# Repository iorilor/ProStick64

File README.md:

# ProStick64

This repository contains everything about the ProStick64 stick replacement module and more!
This is what you can find inside the various folders:
* datasheets:     datasheets of the various electronic components used on the board
* documentation:  useful documents and application notes regarding the STM32G0 MCU
* media:          Images and other media related to ProStick64
* PCB:            PCB gerber files, KICAD project and libraries
* render:         STL files of the enclosure and thumbstick
* source:         Source code of the software

Note: if you want to edit the source code I suggest you to import the source folders inside STM32CubeIDE software.
For any additional info contact me at info@prostick64.com

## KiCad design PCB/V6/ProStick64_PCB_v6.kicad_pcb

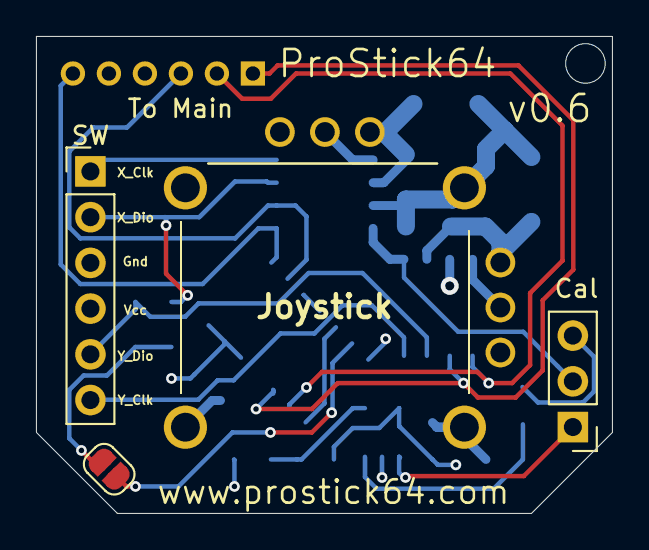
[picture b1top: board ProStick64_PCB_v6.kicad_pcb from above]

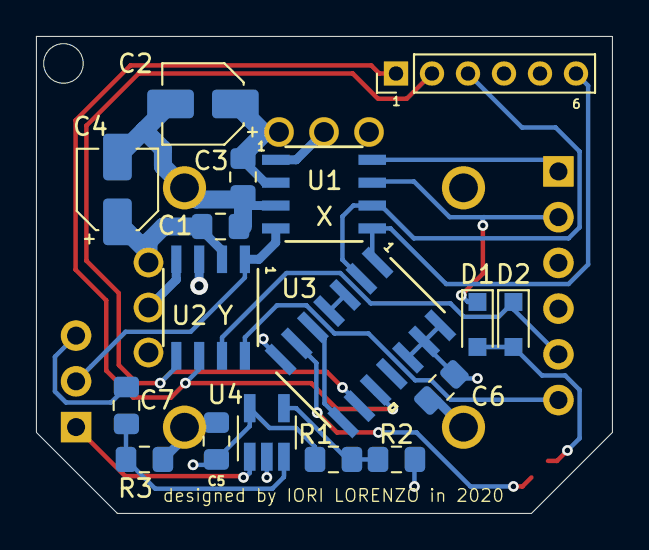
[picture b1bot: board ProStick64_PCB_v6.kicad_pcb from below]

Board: 4 copper layers, 32.0 x 26.5 mm, 21 parts (17 on the bottom side), 20 nets.

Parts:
C1, C3, C5, C6, C7: 0.1uF; C_0805_2012Metric_Pad1.15x1.40mm_HandSolder
C2, C4: 4.7uF; CP_Elec_4x5.3
Cal: CAL_SW; PinHeader_1x03_P2.54mm_Vertical
D1, D2: BAS316; D_SOD-323_HandSoldering
JP1: SolderJumper_2_Open; SolderJumper-2_P1.3mm_Open_RoundedPad1.0x1.5mm
Joystick: RKJXK122000D
R1: 4.75k; R_0805_2012Metric_Pad1.15x1.40mm_HandSolder
R2, R3: 30k; R_0805_2012Metric_Pad1.15x1.40mm_HandSolder
SW: Serial Wire; PinHeader_1x06_P2.54mm_Vertical
To Main: TO MAIN BOARD; PinHeader_1x06_P2.00mm_Vertical
U1: X; STM32G0_SO8_T2
U2: Y; STM32G0_SO8_T2
U3: CD74HC08M
U4: TS861AIL; SOT-23-5_HandSoldering

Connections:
/Vcc: C1.1, C2.1, C3.1, C4.1, C5.1, C6.1, C7.1, Cal.3, Joystick.3, Joystick.6, R1.2, SW.4, To Main.5, U1.2, U2.2, U3.12, U3.13, U3.14, U4.5
/X0: To Main.6, U1.5, U3.1
/X1: To Main.3, U1.6, U3.2
/Y0: To Main.2, U2.5, U3.9
/Y1: To Main.1, U2.6, U3.10
/cal: Cal.2, U1.4, U2.1
/x_dio: D1.1, SW.2, U1.7
/y_dio: D2.1, SW.5, U2.7
GND: C1.2, C2.2, C3.2, C4.2, C5.2, C6.2, Joystick.1, Joystick.4, Joystick.GND, R2.1, R3.2, SW.3, To Main.4, U1.3, U2.3, U3.7, U4.2
unnamed: C7.2, R3.1, U4.3
unnamed: D1.2, D2.2, JP1.1
unnamed: SW.1, U1.8
unnamed: SW.6, U2.8
unnamed: Cal.1, U4.1
unnamed: JP1.2, U3.6
unnamed: R1.1, R2.2, U4.4
unnamed: Joystick.2, U1.1
unnamed: Joystick.5, U2.4
unnamed: U3.3, U3.4
unnamed: U3.5, U3.8

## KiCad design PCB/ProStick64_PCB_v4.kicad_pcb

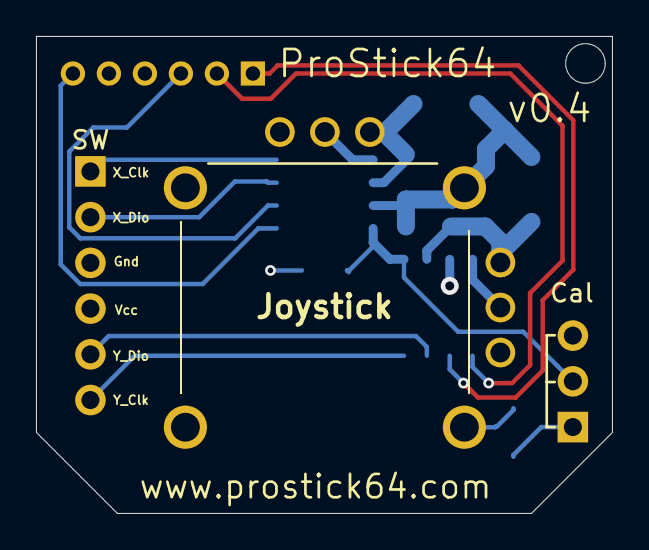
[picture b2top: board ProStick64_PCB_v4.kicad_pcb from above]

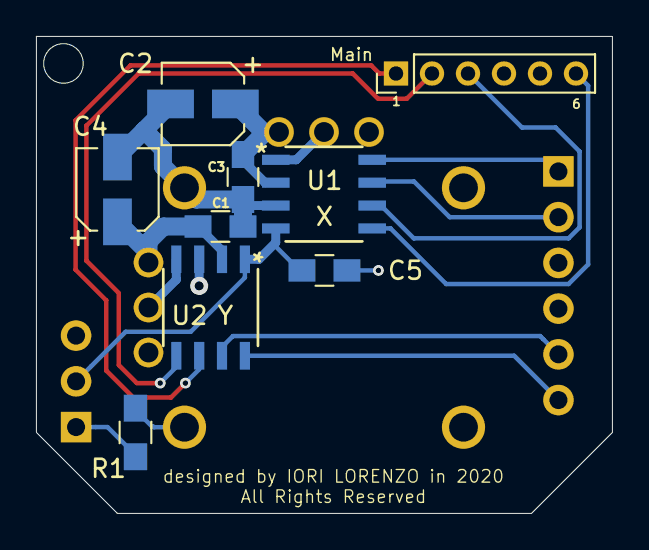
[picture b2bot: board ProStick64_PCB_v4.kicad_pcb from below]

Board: 4 copper layers, 32.0 x 26.5 mm, 12 parts (9 on the bottom side), 14 nets.

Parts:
C1, C3, C5: 0.1uF; C_0805_HandSoldering
C2, C4: 4.7uF; CP_Elec_4x5.3
Cal: CAL_SW; Pin_Header_Straight_1x03_Pitch2.54mm
Joystick: RKJXK122000D
Main: TO MAIN BOARD; Pin_Header_Straight_1x06_Pitch2.00mm
R1: 30k; R_0805_HandSoldering
SW: Serial Wire; Pin_Header_Straight_1x06_Pitch2.54mm
U1: X; STM32G0_SO8_T2
U2: Y; STM32G0_SO8_T2

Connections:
GND: C1.2, C2.2, C3.2, C4.2, Joystick.1, Joystick.4, Main.4, R1.1, SW.3, U1.3, U2.3
unnamed: C1.1, C2.1, C3.1, C4.1, C5.2, Cal.3, Joystick.3, Joystick.6, Main.5, SW.4, U1.2, U2.2
unnamed: C5.1, Cal.2, U1.4, U2.1
unnamed: SW.1, U1.8
unnamed: SW.2, U1.7
unnamed: SW.5, U2.7
unnamed: SW.6, U2.8
unnamed: Cal.1, R1.2
unnamed: Main.1, U2.6
unnamed: Main.2, U2.5
unnamed: Main.3, U1.6
unnamed: Main.6, U1.5
unnamed: Joystick.2, U1.1
unnamed: Joystick.5, U2.4

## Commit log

2020-07-22 Applied guidelines. draw() funtion is now draw(n) where n is the times to repeat. getCalFlashSlot now do only its task, calibration is cast from main function. MAX_RANGE changed from 90 to 93
2020-07-22 Added logo to master branch
2020-07-22 Added logo to dev branch
2020-07-22 Added README.md
2020-07-22 Calibration 3.0 Now the MCUs wait for each other before proceeding during calibration
2020-07-22 Removed .DS store files
2020-07-22 removed ToDo.txt
2020-08-07 Cleaned up media folder
2020-10-20 PCB v0.6 - Added comparator
2020-11-17 PCB_v6
2020-12-29 Source v3
2021-10-03 Prototype Release
2021-10-05 Media Upload
2021-10-05 .DS_Store clear

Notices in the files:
PCB/ProStick64_PCB_v4.kicad_pcb:
All Rights Reserved
parts and their libraries:
Copyright 2016 Accelerated Designs. All rights reserved.
